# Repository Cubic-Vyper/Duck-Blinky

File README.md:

# Duck-Blinky
This is a duck shaped led chaser, I chose to make it shaped as a duck because I love ducks.

Stasis Page PDF (cuz you would need an account to view the page): https://github.com/Cubic-Vyper/Duck-Blinky/blob/fc39c694c192e888ad827d875bb895b51e32edd1/Stasis_ProjectPage-DUCK%20BLINKY.pdf

Demo Video: [https://youtu.be/D5GGE8MXA40](https://youtu.be/D5GGE8MXA40)

# Bill Of Materials

| Name | Purpose | Quantity | Total Cost (USD) | Link to Listing | Distributor |
|------|---------|----------|------------------|----------------|-------------|
| PCB | This will connect everything | 5 | 4.00 | [Link to Listing](http://jlcpcb.com/) | JLCPCB |

The edge of the pcb is a exposed soldering pad because it looks cool.
To power the pcb conect 5v power and ground to the 2-pin connector, rotate the screw to adjust the speed of the lights.
PCB:

schematic:

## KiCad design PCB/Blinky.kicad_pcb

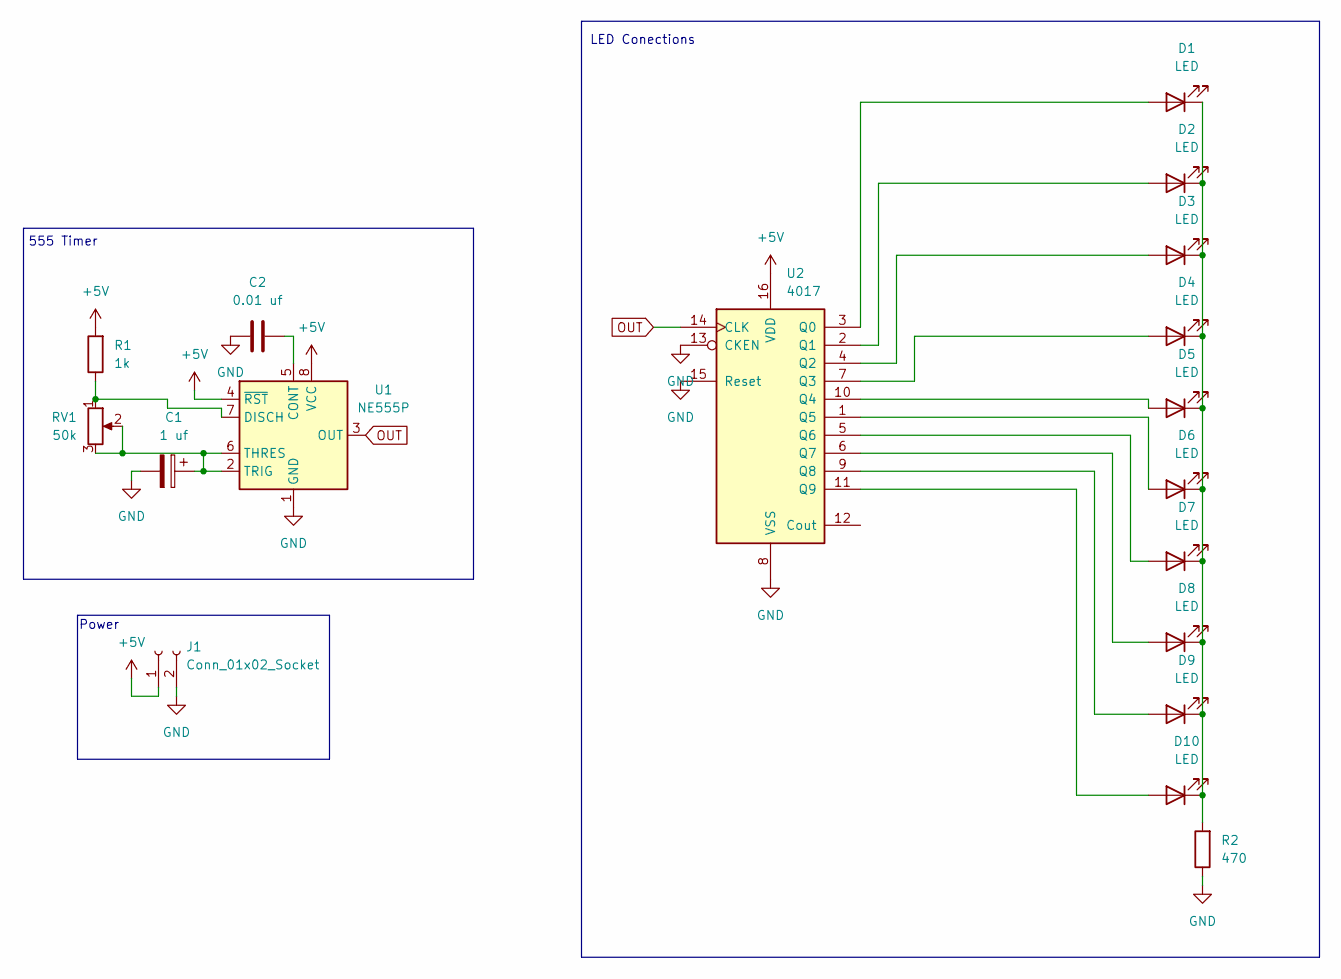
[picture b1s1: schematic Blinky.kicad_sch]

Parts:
C1: 1 uf; CP_Radial_D5.0mm_P2.00mm
C2: 0.01 uf; C_Disc_D7.5mm_W2.5mm_P5.00mm
D1, D2, D3, D4, D5, D6, D7, D8, D9, D10: LED; LED_D3.0mm
J1: Conn_01x02_Socket; PinHeader_1x02_P2.54mm_Vertical
R1: 1k; R_Axial_DIN0207_L6.3mm_D2.5mm_P7.62mm_Horizontal
R2: 470; R_Axial_DIN0207_L6.3mm_D2.5mm_P7.62mm_Horizontal
RV1: 50k; Potentiometer_Vishay_T93YA_Vertical
U1: NE555P; DIP-8_W7.62mm
U2: 4017; DIP-16_W7.62mm

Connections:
+5V: J1.1, R1.2, U1.4 (~RST), U1.8 (VCC), U2.16 (VDD)
GND: C1.2, C2.1, J1.2, R2.1, U1.1 (GND), U2.8 (VSS), U2.13 (CKEN), U2.15 (Reset)
unnamed: D1.2 (A), U2.3 (Q0)
unnamed: D1.1 (K), D2.1 (K), D3.1 (K), D4.1 (K), D5.1 (K), D6.1 (K), D7.1 (K), D8.1 (K), D9.1 (K), D10.1 (K), R2.2
unnamed: D2.2 (A), U2.2 (Q1)
unnamed: D3.2 (A), U2.4 (Q2)
unnamed: D4.2 (A), U2.7 (Q3)
unnamed: D5.2 (A), U2.10 (Q4)
unnamed: D6.2 (A), U2.1 (Q5)
unnamed: D7.2 (A), U2.5 (Q6)
unnamed: D8.2 (A), U2.6 (Q7)
unnamed: D9.2 (A), U2.9 (Q8)
unnamed: D10.2 (A), U2.11 (Q9)
unnamed: C2.2, U1.5 (CONT)
unnamed: R1.1, RV1.1, U1.7 (DISCH)
unnamed: C1.1, RV1.2, RV1.3, U1.2 (TRIG), U1.6 (THRES)
OUT: U1.3 (OUT), U2.14 (CLK)

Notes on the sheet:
LED Conections
555 Timer
Power

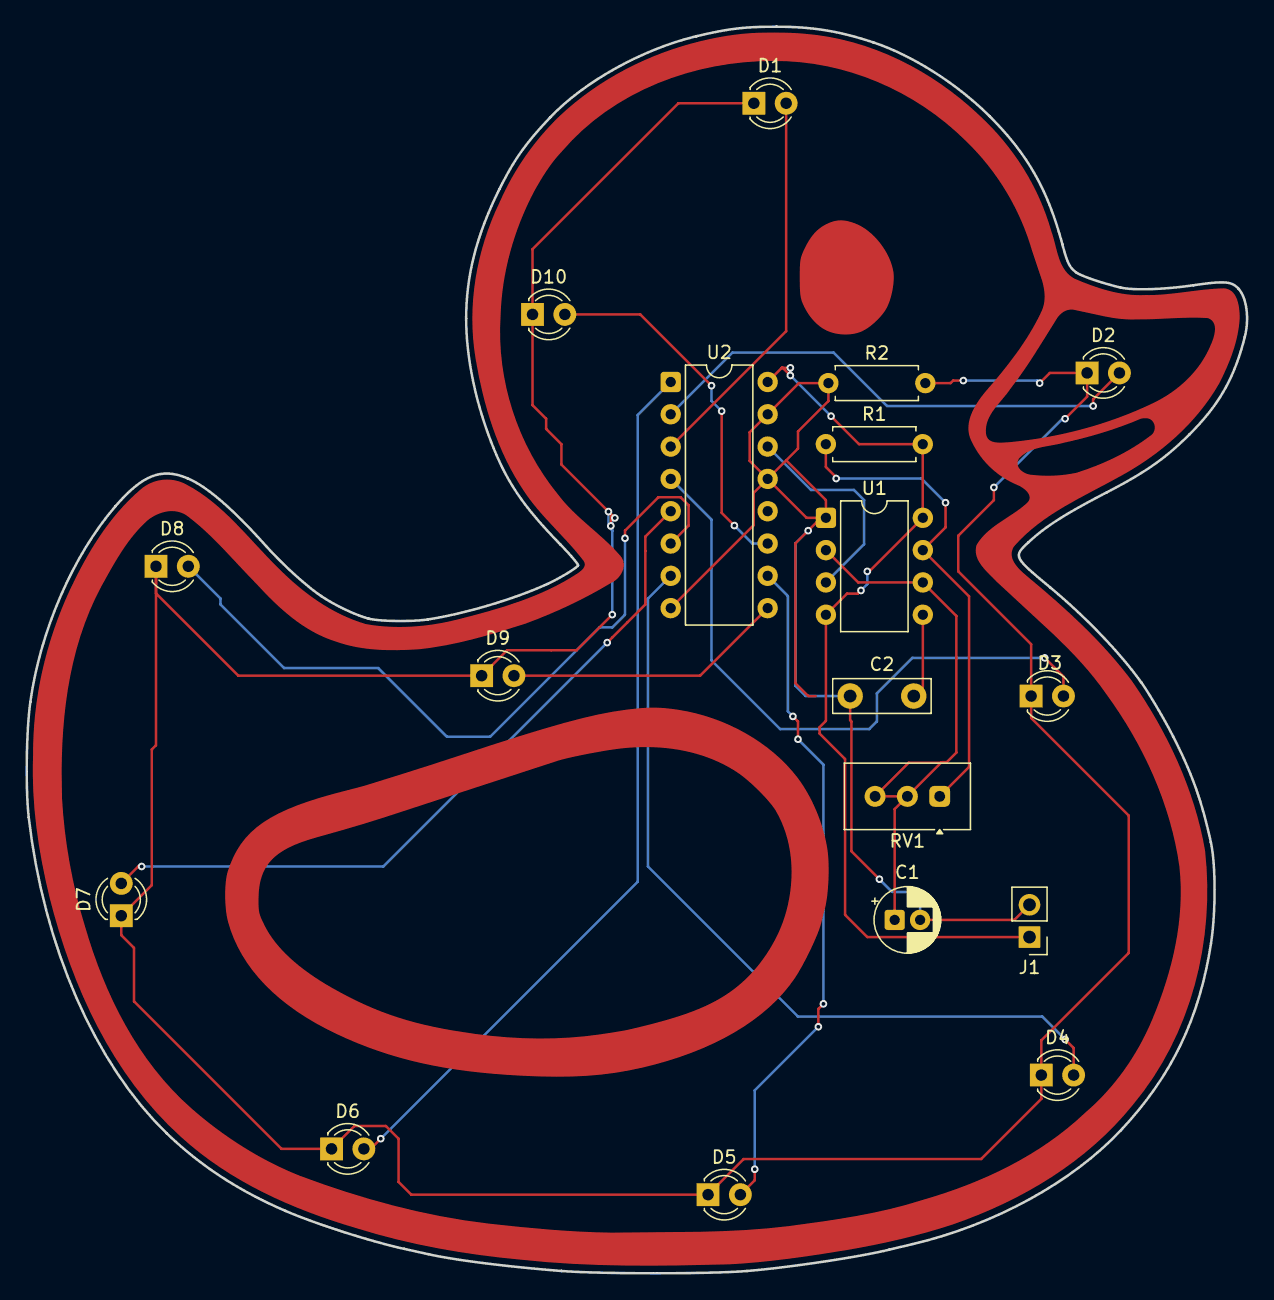
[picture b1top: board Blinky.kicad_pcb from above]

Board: 2 copper layers, 95.9 x 98.0 mm, 18 parts (0 on the bottom side), 17 nets.
